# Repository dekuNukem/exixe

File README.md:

# exixe: Low-cost miniature Nixie tube driver modules

[Get exixe](https://www.tindie.com/products/dekuNukem/exixe-miniture-nixie-tube-driver-modules/) | [User manual](getting_started.md)

exixe is a miniature driver module for IN-12 and IN-14 Nixie tubes.

It aims to simplify Nixie tube related projects by eliminating the need for obscure vintage driver chips and multiplexing circuits. Instead, you can control every digit and the RGB backlight via SPI using only 3 wires and 1 line of code.

exixe is cheap, small and modular for easy integration. It is compatible with Arduino, Raspberry Pi, and virtually all embedded dev boards today.

## Buy exixe on Tindie!

I did a small production run of exixe modules, and now you can buy them directly on Tindie:

https://www.tindie.com/products/dekuNukem/exixe-miniture-nixie-tube-driver-modules/

## Features

Compared to the traditional approach, exixe modules offers significant advantages:

#### Small and modular
* 2x4 cm (0.79x1.57 inches)
* Breadboard friendly
* Easy integration
* Reusable

#### SPI interface
* High speed, up to 24MHz SCLK
* Simple 16-byte command packet
* Available on virtually all embedded systems including Arduino and Raspberry Pi

#### Advanced control
* RGB backlight
* 128 brightness levels
* Hardware PWM on all cathodes and LEDs for smooth dimming and animations

#### Tube overdrive
* Optionally allows twice the cathode current
* For poisoned cathodes in second-hand tubes
* [Before](resources/no_overdrive.jpg) and [after](resources/with_overdrive.jpg).

#### No multiplexing
* Brighter display
* Longer tube life
* Simpler design
* Lower power consumption

## Getting started

Please see [getting_started.md](/getting_started.md)

## Arduino Library

Please [click here](arduino_library)

## Raspberry Pi/Python Library

Please [click here](python_library)

## Pinout, SPI command format and technical details

Please see [technical_details.md](/technical_details.md)

## Supported tubes

exixe-14 module is primarily designed for IN-14 Nixie tubes, but will also work with IN-16 and IN-19 tubes.

exixe-12 module is primarily designed for IN-12 Nixie tubes, but works with IN-15 tubes as well.

## Using other tubes

You can also use exixe module with unsupported tubes, with some modification.

Please see [unsupported_tubes.md](/unsupported_tubes.md)

## Making some yourself

Please see [making_some.md](/making_some.md)

## Contact

Questions? Feel free to [open an issue](https://github.com/dekuNukem/exixe/issues). This is the preferred way since it helps other people too.

You can also email me at `dekunukem gmail com` for inquires.

## More photos

exixe-12 working with an Arduino Micro, showing a smooth crossfade animation:

exixe-14 in action on a [finished clock](https://github.com/dekuNukem/exixe_clock):

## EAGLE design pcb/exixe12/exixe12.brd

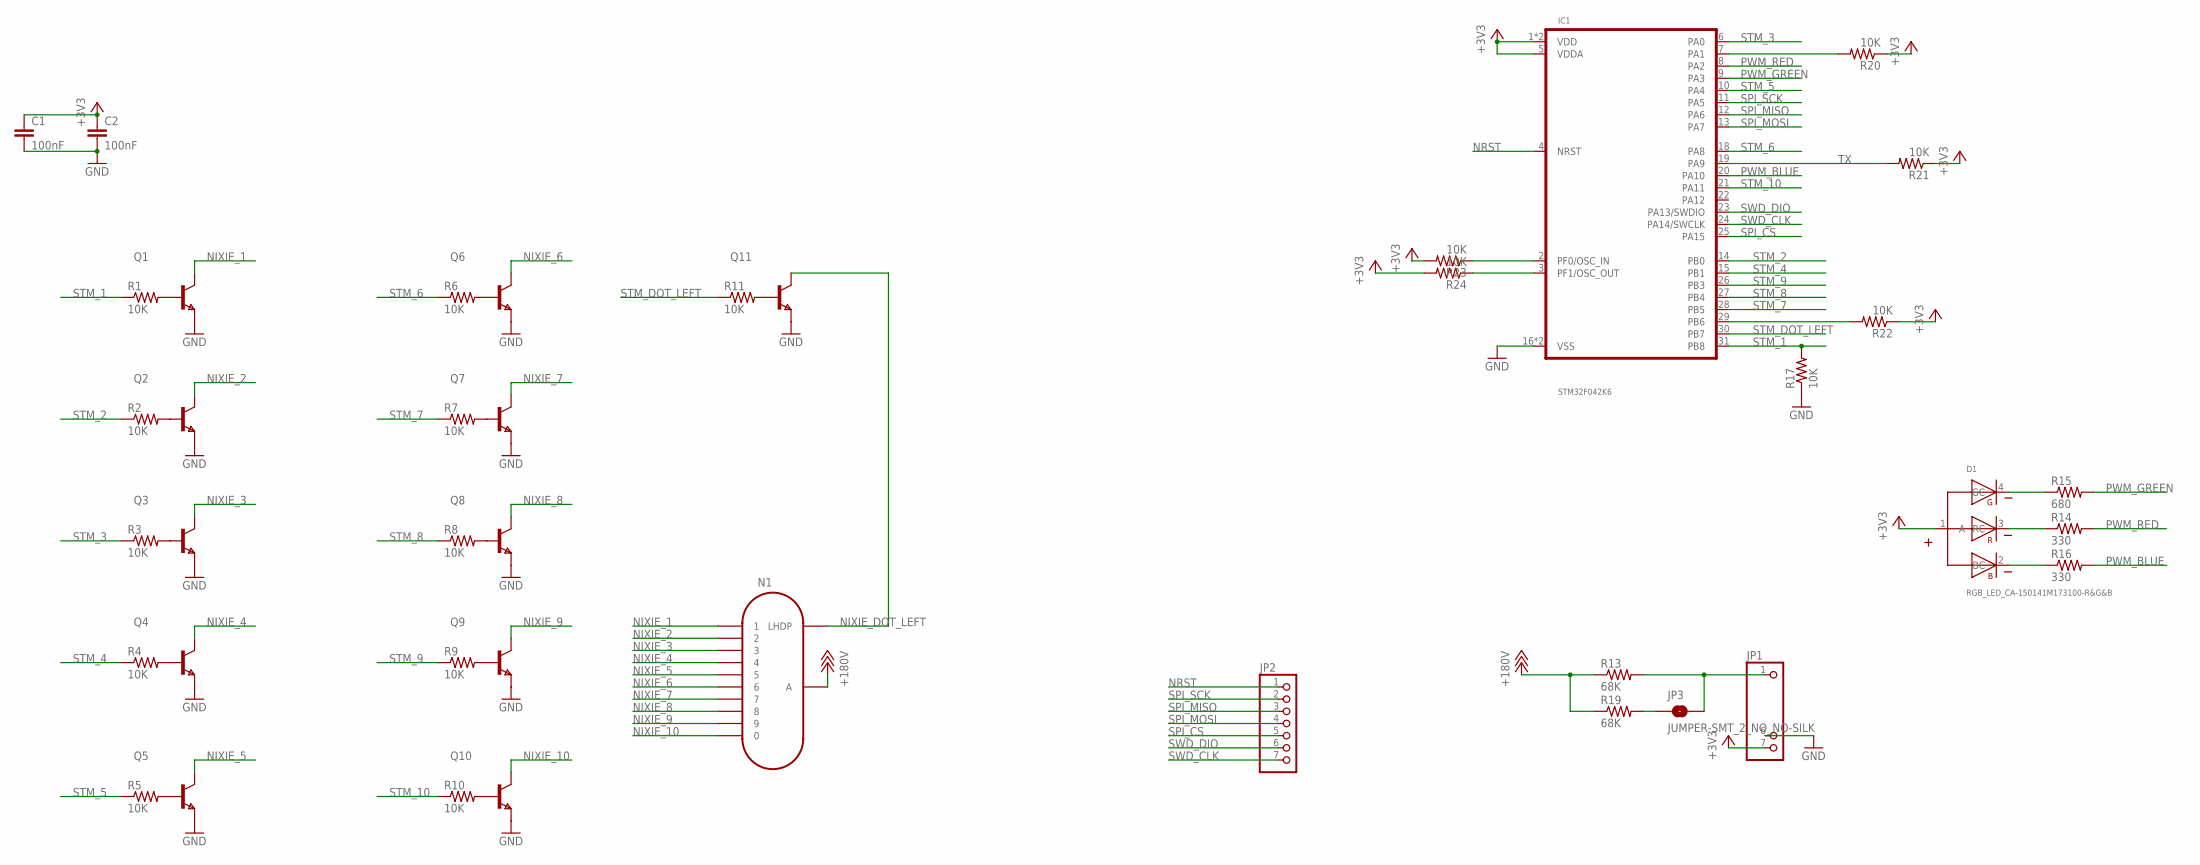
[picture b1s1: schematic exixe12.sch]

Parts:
C1, C2: 100nF; 0805
D1: RGB_LED_CA-150141M173100-R&G&B; 3528-COMMON-ANODE
IC1: STM32F042K6; TQFP32-08
JP1, JP2: PINHD-1X7; 1X07
JP3: JUMPER-SMT_2_NO_NO-SILK; SMT-JUMPER_2_NO_NO-SILK
N1: IN-12B; IN-12
Q1, Q2, Q3, Q4, Q5, Q6, Q7, Q8, Q9, Q10, Q11: BF820; SOT323
R1, R2, R3, R4, R5, R6, R7, R8, R9, R10, R11, R17, R20, R21, R22, R23, R24: 10K; 0805
R13, R19: 68K; 0805
R14, R16: 330; 0805
R15: 680; 0805

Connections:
+3V3: C1.1, C2.1, D1.1 (A), IC1.1 (VDD), IC1.5 (VDDA), IC1.17 (VDD), JP1.7, R20.1, R21.1, R22.1, R23.2, R24.2
+180V: N1.A, R13.1, R19.1
GND: C1.2, C2.2, IC1.16 (VSS), IC1.32 (VSS), JP1.6, Q1.2 (E), Q2.2 (E), Q3.2 (E), Q4.2 (E), Q5.2 (E), Q6.2 (E), Q7.2 (E), Q8.2 (E), Q9.2 (E), Q10.2 (E), Q11.2 (E), R17.1
unnamed: Q1.1 (B), R1.2
unnamed: JP3.1, R19.2
unnamed: D1.4 (GC), R15.1
unnamed: Q2.1 (B), R2.2
unnamed: Q3.1 (B), R3.2
unnamed: Q4.1 (B), R4.2
unnamed: Q5.1 (B), R5.2
unnamed: Q6.1 (B), R6.2
unnamed: Q7.1 (B), R7.2
unnamed: Q8.1 (B), R8.2
unnamed: Q9.1 (B), R9.2
unnamed: Q10.1 (B), R10.2
unnamed: Q11.1 (B), R11.2
unnamed: IC1.29 (PB6), R22.2
unnamed: D1.3 (RC), R14.1
unnamed: IC1.2 (PF0/OSC_IN), R23.1
unnamed: IC1.3 (PF1/OSC_OUT), R24.1
unnamed: JP1.1, JP3.2, R13.2
unnamed: IC1.7 (PA1), R20.2
unnamed: D1.2 (BC), R16.1
NIXIE_1: N1.1, Q1.3 (C)
NIXIE_2: N1.2, Q2.3 (C)
NIXIE_3: N1.3, Q3.3 (C)
NIXIE_4: N1.4, Q4.3 (C)
NIXIE_5: N1.5, Q5.3 (C)
NIXIE_6: N1.6, Q6.3 (C)
NIXIE_7: N1.7, Q7.3 (C)
NIXIE_8: N1.8, Q8.3 (C)
NIXIE_9: N1.9, Q9.3 (C)
NIXIE_10: N1.0, Q10.3 (C)
NIXIE_DOT_LEFT: N1.LHDP, Q11.3 (C)
NRST: IC1.4 (NRST), JP2.1
PWM_BLUE: IC1.20 (PA10), R16.2
PWM_GREEN: IC1.9 (PA3), R15.2
PWM_RED: IC1.8 (PA2), R14.2
SPI_CS: IC1.25 (PA15), JP2.5
SPI_MISO: IC1.12 (PA6), JP2.3
SPI_MOSI: IC1.13 (PA7), JP2.4
SPI_SCK: IC1.11 (PA5), JP2.2
STM_1: IC1.31 (PB8), R1.1, R17.2
STM_2: IC1.14 (PB0), R2.1
STM_3: IC1.6 (PA0), R3.1
STM_4: IC1.15 (PB1), R4.1
STM_5: IC1.10 (PA4), R5.1
STM_6: IC1.18 (PA8), R6.1
STM_7: IC1.28 (PB5), R7.1
STM_8: IC1.27 (PB4), R8.1
STM_9: IC1.26 (PB3), R9.1
STM_10: IC1.21 (PA11), R10.1
STM_DOT_LEFT: IC1.30 (PB7), R11.1
SWD_CLK: IC1.24 (PA14/SWCLK), JP2.7
SWD_DIO: IC1.23 (PA13/SWDIO), JP2.6
TX: IC1.19 (PA9), R21.2

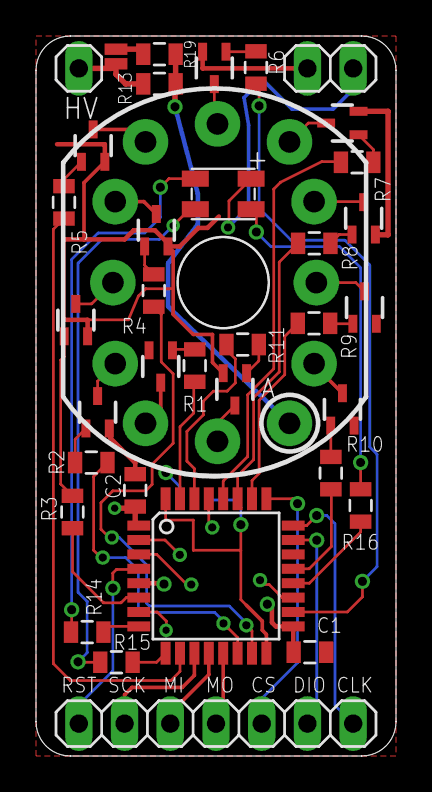
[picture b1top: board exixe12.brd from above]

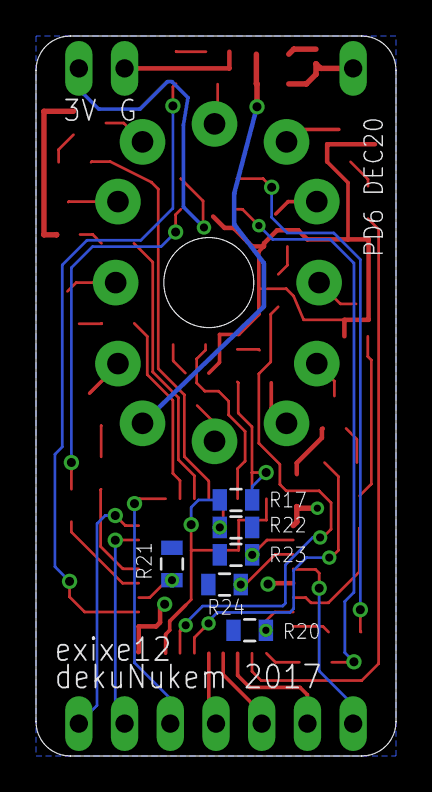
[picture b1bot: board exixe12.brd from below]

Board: 2 copper layers, 20.0 x 40.0 mm, 41 parts (6 on the bottom side), 56 nets.

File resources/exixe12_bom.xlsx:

Part | Value | Device | Package | Description
C1 | 1uF | CAP0805 | 0805 | Capacitor
C2 | 100nF | CAP0805 | 0805 | Capacitor
D1 | RGB LED | RGB_LED | 3528-COMMON-ANODE | SMD full-color LED
JP1 |  | PINHD-1X7 | 1X07 | PIN HEADER
JP2 |  | PINHD-1X7 | 1X07 | PIN HEADER
N1 | IN-12B | IN-12B | IN-12 | IN-12B: medium numeric topview nixie tube
Q1 |  | BF820 | SOT323 | NPN TRANSISTOR
Q2 |  | BF820 | SOT323 | NPN TRANSISTOR
Q3 |  | BF820 | SOT323 | NPN TRANSISTOR
Q4 |  | BF820 | SOT323 | NPN TRANSISTOR
Q5 |  | BF820 | SOT323 | NPN TRANSISTOR
Q6 |  | BF820 | SOT323 | NPN TRANSISTOR
Q7 |  | BF820 | SOT323 | NPN TRANSISTOR
Q8 |  | BF820 | SOT323 | NPN TRANSISTOR
Q9 |  | BF820 | SOT323 | NPN TRANSISTOR
Q10 |  | BF820 | SOT323 | NPN TRANSISTOR
Q11 |  | BF820 | SOT323 | NPN TRANSISTOR
R1 | 10K | RESISTOR0805-RES | 0805 | Resistor
R2 | 10K | RESISTOR0805-RES | 0805 | Resistor
R3 | 10K | RESISTOR0805-RES | 0805 | Resistor
R4 | 10K | RESISTOR0805-RES | 0805 | Resistor
R5 | 10K | RESISTOR0805-RES | 0805 | Resistor
R6 | 10K | RESISTOR0805-RES | 0805 | Resistor
R7 | 10K | RESISTOR0805-RES | 0805 | Resistor
R8 | 10K | RESISTOR0805-RES | 0805 | Resistor
R9 | 10K | RESISTOR0805-RES | 0805 | Resistor
R10 | 10K | RESISTOR0805-RES | 0805 | Resistor
R11 | 10K | RESISTOR0805-RES | 0805 | Resistor
R12 | 68K | RESISTOR0805-RES | 0805 | Resistor
R13 | 68K | RESISTOR0805-RES | 0805 | Resistor
R14 | 330 | RESISTOR0805-RES | 0805 | Resistor
R15 | 680 | RESISTOR0805-RES | 0805 | Resistor
R16 | 330 | RESISTOR0805-RES | 0805 | Resistor
R17 | 68K | RESISTOR0805-RES | 0805 | Resistor
R18 | 10K | RESISTOR0805-RES | 0805 | Resistor
R19 | 68K | RESISTOR0805-RES | 0805 | Resistor
U$2 | STM32F042K6T6 | STM32F042K6T6 | TQFP32-08 | STM32 microcontroller

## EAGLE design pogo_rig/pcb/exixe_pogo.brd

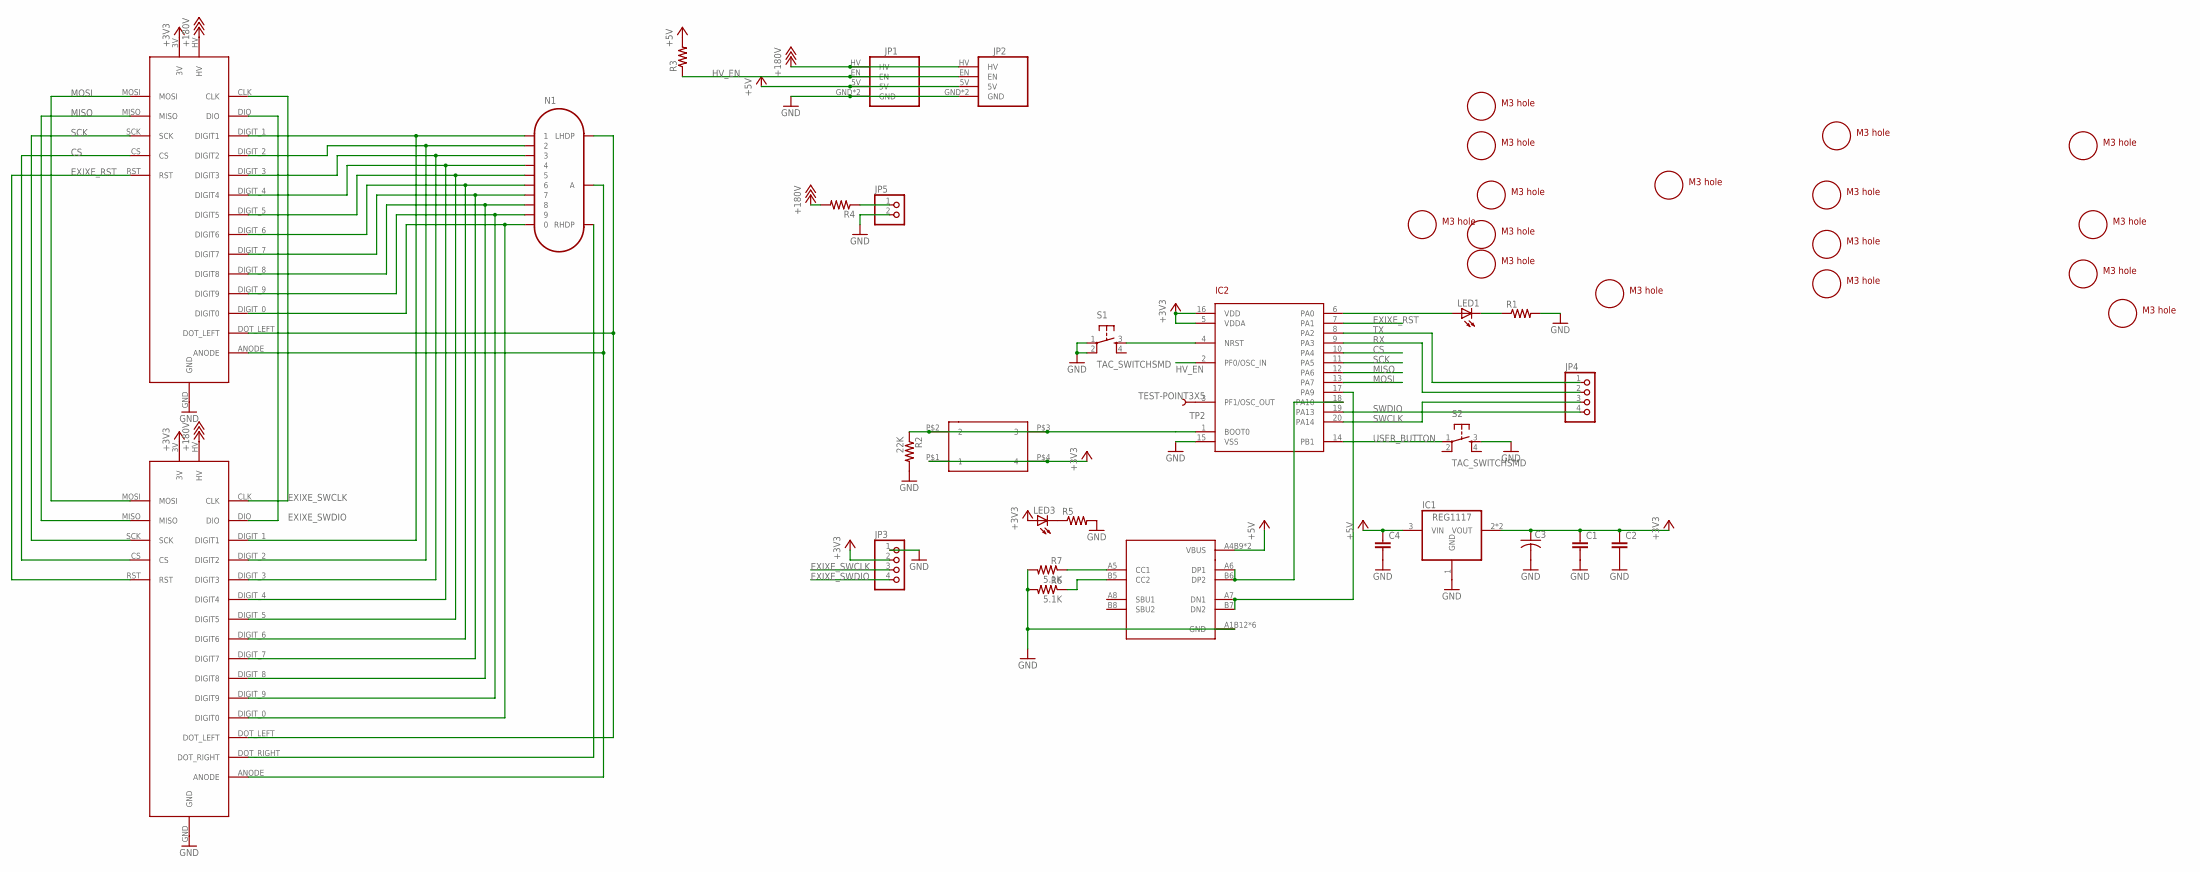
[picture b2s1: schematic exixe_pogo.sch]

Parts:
C1, C2, C4: CAP0805; 0805
C3: C-USC1210; C1210
IC1: REG1117; SOT223
IC2: STM32F030F4; TSSOP20
JP1: EBAY_MODULEEBAY; EBAY_PKG
JP2: EBAY_MODULETAOBAO; TAOBAO_PKG
JP3, JP4: PINHD-1X4; 1X04
JP5: PINHD-1X2; 1X02
LED1, LED3: LEDCHIP-LED0805; CHIP-LED0805
N1: IN-14
R1, R3, R4, R5: RESISTOR0805-RES; 0805
R2: 22K; 0805
R6, R7: 5.1K; 0805
S1, S2: TAC_SWITCHSMD; TACTILE-SWITCH-SMD
SW2: 324_SW324_SWITCH_FOOT_HOLE; 342_SWICH_FOOT_HOLE
TP2: TEST-POINT3X5; PAD.03X.05
U1: USBC_16P_CENTERED; USBC_16P_FOOT
U$1: EXIXE12_POGO; EXIXE12_PAC
U$2: EXIXE14_POGO; EXIXE14_PAC
U$3, U$4, U$5, U$6, U$7, U$8, U$9, U$10, U$11, U$12, U$13, U$14, U$15, U$16, U$17, U$18: M3_MOUNTING_HOLE; M3_MOUNTING_HOLE_PACK

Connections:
+3V3: C1.1, C2.1, C3.1, IC1.2 (VOUT), IC1.4 (VOUT), IC2.5 (VDDA), IC2.16 (VDD), JP3.2, LED3.A, SW2.P$1 (1), SW2.P$4 (4), U$1.3V, U$2.3V
+5V: C4.1, IC1.3 (VIN), JP1.5V, JP2.5V, R3.2, U1.A4B9 (VBUS), U1.B4A9 (VBUS)
+180V: JP1.HV, JP2.HV, R4.2, U$1.HV, U$2.HV
CS: IC2.10 (PA4), U$1.CS, U$2.CS
EXIXE_RST: IC2.7 (PA1), U$1.RST, U$2.RST
EXIXE_SWCLK: JP3.3, U$1.CLK, U$2.CLK
EXIXE_SWDIO: JP3.4, U$1.DIO, U$2.DIO
GND: C1.2, C2.2, C3.2, C4.2, IC1.1 (GND), IC2.15 (VSS), JP1.GND, JP1.GND2 (GND), JP2.GND, JP2.GND2 (GND), JP3.1, JP5.2, R1.2, R2.2, R5.2, R6.2, R7.2, S1.1, S1.2, S2.3, U1.A1B12 (GND), U1.B11A12 (GND), U1.P$13 (GND), U1.P$14 (GND), U1.P$15 (GND), U1.P$16 (GND), U$1.GND, U$2.GND
HV_EN: IC2.2 (PF0/OSC_IN), JP1.EN, JP2.EN, R3.1
MISO: IC2.12 (PA6), U$1.MISO, U$2.MISO
MOSI: IC2.13 (PA7), U$1.MOSI, U$2.MOSI
unnamed: N1.1, U$1.DIGIT_1 (DIGIT1), U$2.DIGIT_1 (DIGIT1)
unnamed: IC2.4 (NRST), S1.3
unnamed: N1.2, U$1.DIGIT_2 (DIGIT2), U$2.DIGIT_2 (DIGIT2)
unnamed: N1.3, U$1.DIGIT_3 (DIGIT3), U$2.DIGIT_3 (DIGIT3)
unnamed: N1.4, U$1.DIGIT_4 (DIGIT4), U$2.DIGIT_4 (DIGIT4)
unnamed: N1.5, U$1.DIGIT_5 (DIGIT5), U$2.DIGIT_5 (DIGIT5)
unnamed: N1.6, U$1.DIGIT_6 (DIGIT6), U$2.DIGIT_6 (DIGIT6)
unnamed: N1.7, U$1.DIGIT_7 (DIGIT7), U$2.DIGIT_7 (DIGIT7)
unnamed: N1.8, U$1.DIGIT_8 (DIGIT8), U$2.DIGIT_8 (DIGIT8)
unnamed: N1.9, U$1.DIGIT_9 (DIGIT9), U$2.DIGIT_9 (DIGIT9)
unnamed: N1.0, U$1.DIGIT_0 (DIGIT0), U$2.DIGIT_0 (DIGIT0)
unnamed: N1.RHDP, U$2.DOT_RIGHT
unnamed: N1.LHDP, U$1.DOT_LEFT, U$2.DOT_LEFT
unnamed: N1.A, U$1.ANODE, U$2.ANODE
unnamed: LED1.C, R1.1
unnamed: IC2.6 (PA0), LED1.A
unnamed: JP5.1, R4.1
unnamed: IC2.18 (PA10), U1.A6 (DP1), U1.B6 (DP2)
unnamed: IC2.17 (PA9), U1.A7 (DN1), U1.B7 (DN2)
unnamed: IC2.3 (PF1/OSC_OUT), TP2.P$1
unnamed: IC2.1 (BOOT0), R2.1, SW2.P$2 (2), SW2.P$3 (3)
unnamed: R6.1, U1.B5 (CC2)
unnamed: R7.1, U1.A5 (CC1)
unnamed: LED3.C, R5.1
RX: IC2.9 (PA3), JP4.2
SCK: IC2.11 (PA5), U$1.SCK, U$2.SCK
SWCLK: IC2.20 (PA14), JP4.3
SWDIO: IC2.19 (PA13), JP4.4
TX: IC2.8 (PA2), JP4.1
USER_BUTTON: IC2.14 (PB1), S2.1

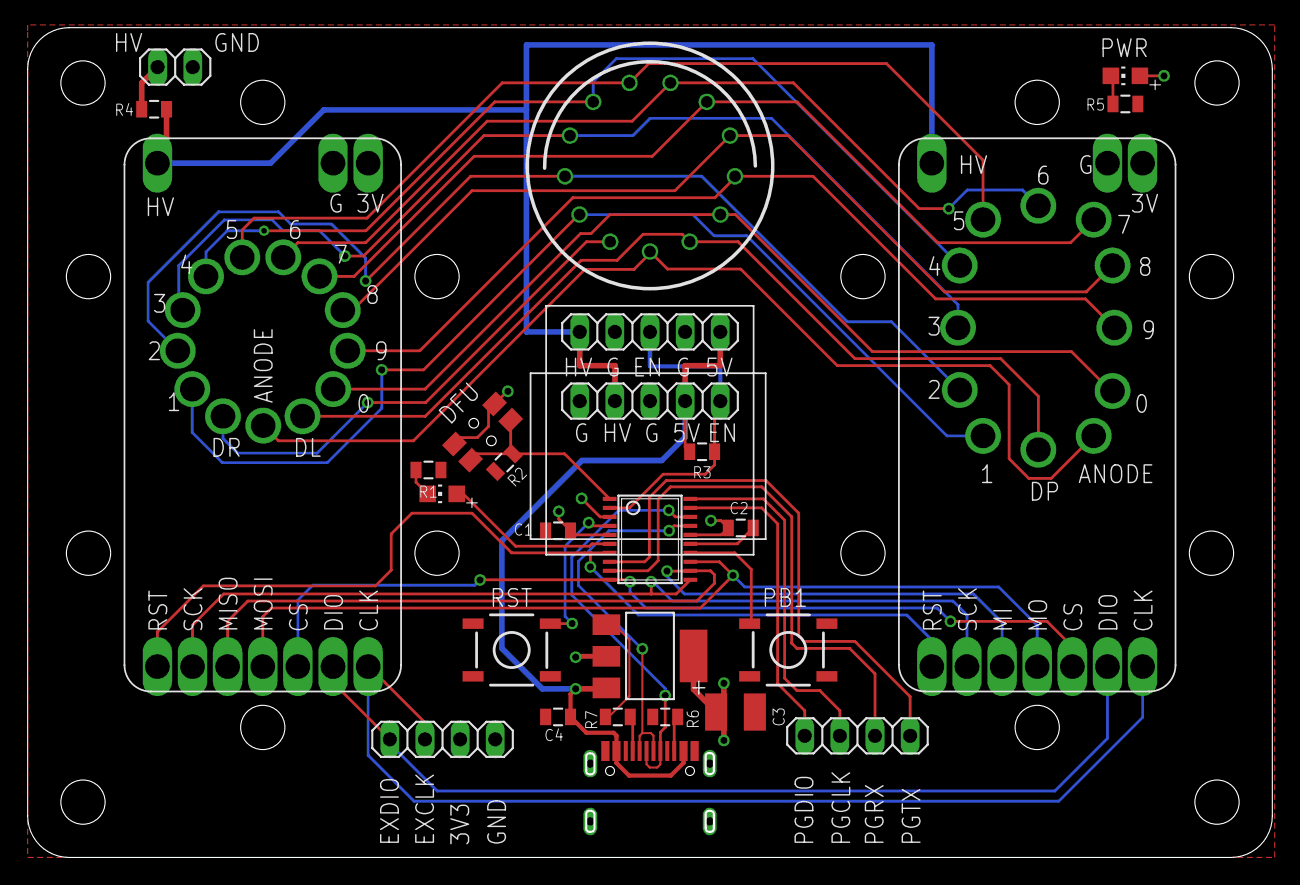
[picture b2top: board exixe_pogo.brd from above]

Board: 2 copper layers, 90.0 x 60.0 mm, 44 parts (1 on the bottom side), 41 nets.

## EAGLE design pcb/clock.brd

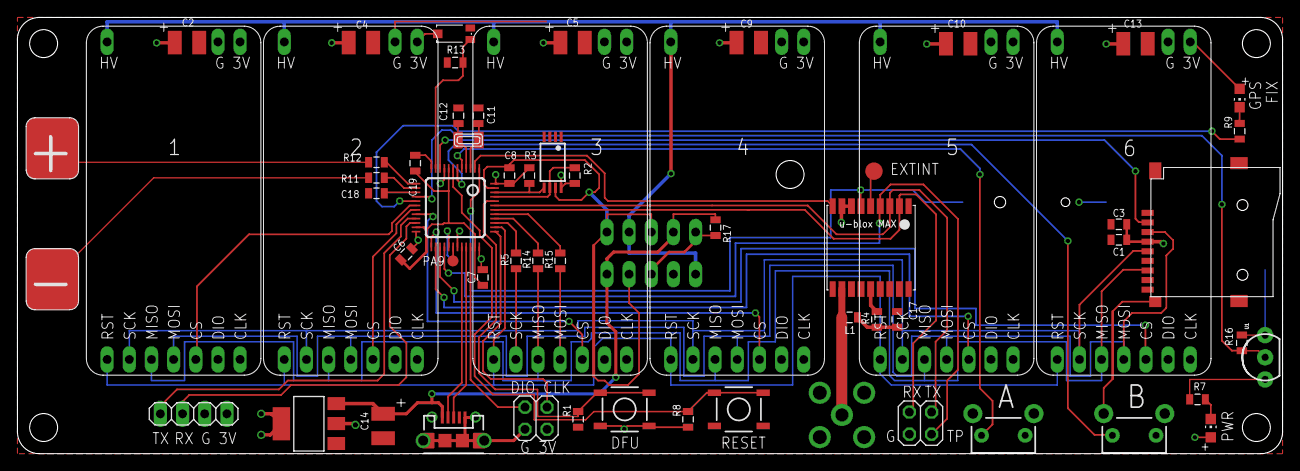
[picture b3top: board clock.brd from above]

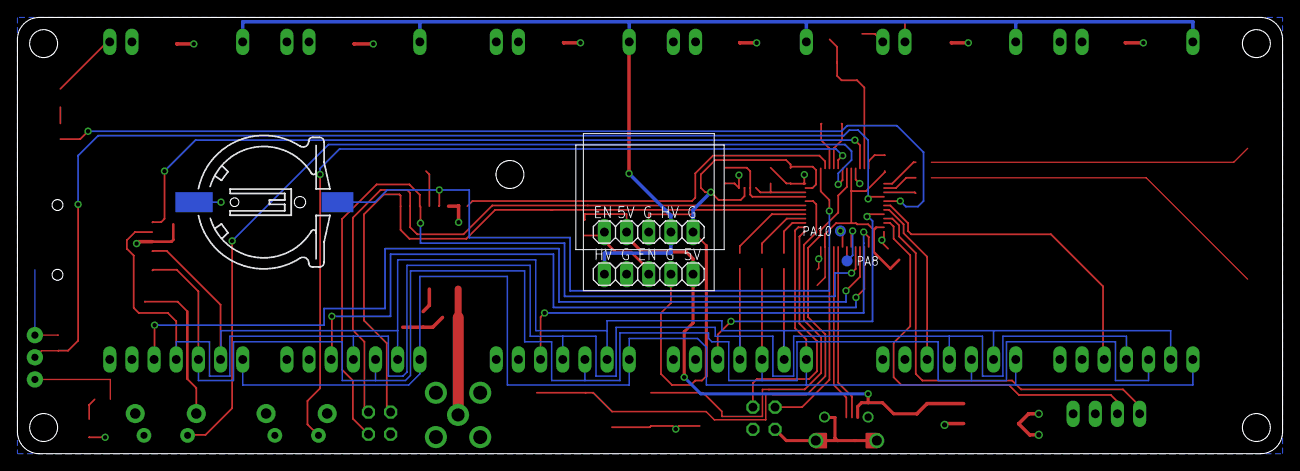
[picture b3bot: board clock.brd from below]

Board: 2 copper layers, 145.0 x 50.0 mm, 72 parts (5 on the bottom side), 56 nets.

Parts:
C1, C3, C6, C7, C8, C11, C12, C17, C18, C19: 0805
C2, C4, C5, C9, C10, C13, C14: C1210
G1: CH291-1220LF
IC1: STM32F072C8T6; TQFP48
IC2: REG1117; SOT223
IC3: 24C64ST; TSSOP8
JP1: EBAY_PKG
JP2: TAOBAO_PKG
JP3, JP4: 2X02
JP5: 1X04
L1: 0805
LED2: CHIP-LED0805
PWR: CHIP-LED0805
R1, R2, R3, R4, R5, R7, R8, R9, R11, R12, R13, R14, R15, R16, R17: 0805
S1, S2: TAC_SWITCHSMD; TACTILE-SWITCH-SMD
S4, S5: SWITCH-MOMENTARY-2SIDE_EZ; TACTILE-PTH-SIDEEZ
SD1: TF-HOLDER; TF-PULL
TP1: PTR1TP20R; TP20R
TP2, TP3, TP4: TEST-POINT3X5; PAD.03X.05
U1: DS18B20; TO-92-AMMO
U$1, U$2, U$3, U$4, U$5, U$6: EXIXE; EXIXE_PAC
U$7: MAX-M8
U$8: TEMT6000; TEMT6000-SEN
U$10, U$11, U$12, U$13, U$20: M3_MOUNTING_HOLE; M3_MOUNTING_HOLE_PACK
U$14, U$15: TOUCHPAD; TOUCHPAD_PAK
X1: SMA90_DIP
X2: XTAL3215
X3: USB-MICROB

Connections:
+3V3: C1.1, C2.1, C3.1, C4.1, C5.1, C6.1, C7.1, C8.1, C9.1, C10.1, C13.1, IC1.9, IC1.24, IC1.36, IC1.48, IC2.2, IC2.4, IC3.8, JP3.3, JP5.4, LED2.A, PWR.A, R2.2, R3.2, R8.2, R16.2, S1.3, S1.4, SD1.4, U1.3, U$1.3V, U$2.3V, U$3.3V, U$4.3V, U$5.3V, U$6.3V, U$7.7_VCC_IO, U$7.8_VCC, U$8.COLLECTOR
+5V: C14.1, IC2.3, JP1.5V, JP2.5V, R17.2, X3.VBUS
+180V: JP1.HV, JP2.HV, U$1.HV, U$2.HV, U$3.HV, U$4.HV, U$5.HV, U$6.HV
A_BUTTON: IC1.5, S4.1
B_BUTTON: IC1.6, S5.1
DS18B20_DATA: IC1.16, R16.1, U1.2
EXIXE1_CS: IC1.18, U$1.CS
EXIXE2_CS: IC1.19, U$2.CS
EXIXE3_CS: IC1.20, U$3.CS
EXIXE4_CS: IC1.25, U$4.CS
EXIXE5_CS: IC1.26, U$5.CS
EXIXE6_CS: IC1.27, U$6.CS
EXIXE_RESET: IC1.38, U$1.RST, U$2.RST, U$3.RST, U$4.RST, U$5.RST, U$6.RST
GND: C1.2, C2.2, C3.2, C4.2, C5.2, C6.2, C7.2, C8.2, C9.2, C10.2, C11.2, C12.2, C13.2, C14.2, C17.2, C18.1, C19.2, G1.-, IC1.8, IC1.23, IC1.35, IC1.47, IC2.1, IC3.1, IC3.2, IC3.3, IC3.4, IC3.7, JP1.GND, JP1.GND2, JP2.GND, JP2.GND2, JP3.1, JP4.1, JP5.3, R1.2, R7.1, R13.1, S2.3, S2.4, S4.2, S4.ANCHOR1, S4.ANCHOR2, S5.2, S5.ANCHOR1, S5.ANCHOR2, SD1.6, SD1.S1, SD1.S2, SD1.S3, SD1.S4, U1.1, U$1.GND, U$2.GND, U$3.GND, U$4.GND, U$5.GND, U$6.GND, U$7.1_GND, U$7.10_GND, U$7.12_GND, X1.GND1, X1.GND2, X1.GND3, X1.GND4, X3.GND, X3.P1, X3.P2, X3.P3, X3.P4, X3.P5, X3.P6
GPS_FIX_LED: IC1.17, R9.2
GPS_RESET: IC1.2, U$7.9_RESET_N
GPS_TP: IC1.28, JP4.3, U$7.4_TIMEPULSE
I2C_SCL: IC1.45, IC3.6, R2.1
I2C_SDA: IC1.46, IC3.5, R3.1
LIGHT_SENSOR_OUTPUT: IC1.11, R13.2, U$8.EMITTER
unnamed: C11.1, IC1.3, X2.P$2
unnamed: C12.1, IC1.4, X2.P$1
unnamed: IC1.7, R8.1, S2.1, S2.2
unnamed: L1.1, U$7.11_RF_IN, X1.ANTENNA
unnamed: IC1.44, R1.1, S1.1, S1.2
unnamed: IC1.31, TP2.P$1
unnamed: IC1.30, TP3.P$1
unnamed: IC1.14, R11.1
unnamed: R11.2, U$15.P$1
unnamed: R12.2, U$14.P$1
unnamed: IC1.13, R12.1
unnamed: C17.1, L1.2, R4.2
unnamed: R4.1, U$7.14_VCC_RF
unnamed: C18.2, IC1.15
unnamed: IC1.29, TP4.P$1
unnamed: IC1.39, R5.1
unnamed: C19.1, IC1.12
unnamed: IC1.41, R15.1
unnamed: IC1.40, R14.1
unnamed: LED2.C, R9.1
unnamed: TP1.TP, U$7.5_EXTINT
unnamed: PWR.C, R7.2
NIXIE_PWR_EN: JP1.EN, JP2.EN, R17.1
PB10: IC1.21, JP5.1
PB11: IC1.22, JP5.2
SD_CS: IC1.10, SD1.2
SPI1_MISO: R14.2, SD1.7, U$1.MISO, U$2.MISO, U$3.MISO, U$4.MISO, U$5.MISO, U$6.MISO
SPI1_MOSI: R15.2, SD1.3, U$1.MOSI, U$2.MOSI, U$3.MOSI, U$4.MOSI, U$5.MOSI, U$6.MOSI
SPI1_SCK: R5.2, SD1.5, U$1.SCK, U$2.SCK, U$3.SCK, U$4.SCK, U$5.SCK, U$6.SCK
SWCLK: IC1.37, JP3.4
SWDIO: IC1.34, JP3.2
USART1_RX: IC1.43, JP4.4, U$7.3_RXD
USART1_TX: IC1.42, JP4.2, U$7.2_TXD
USB_DM: IC1.32, X3.D-
USB_DP: IC1.33, X3.D+
VBAT: G1.+, IC1.1, U$7.6_V_BCKP

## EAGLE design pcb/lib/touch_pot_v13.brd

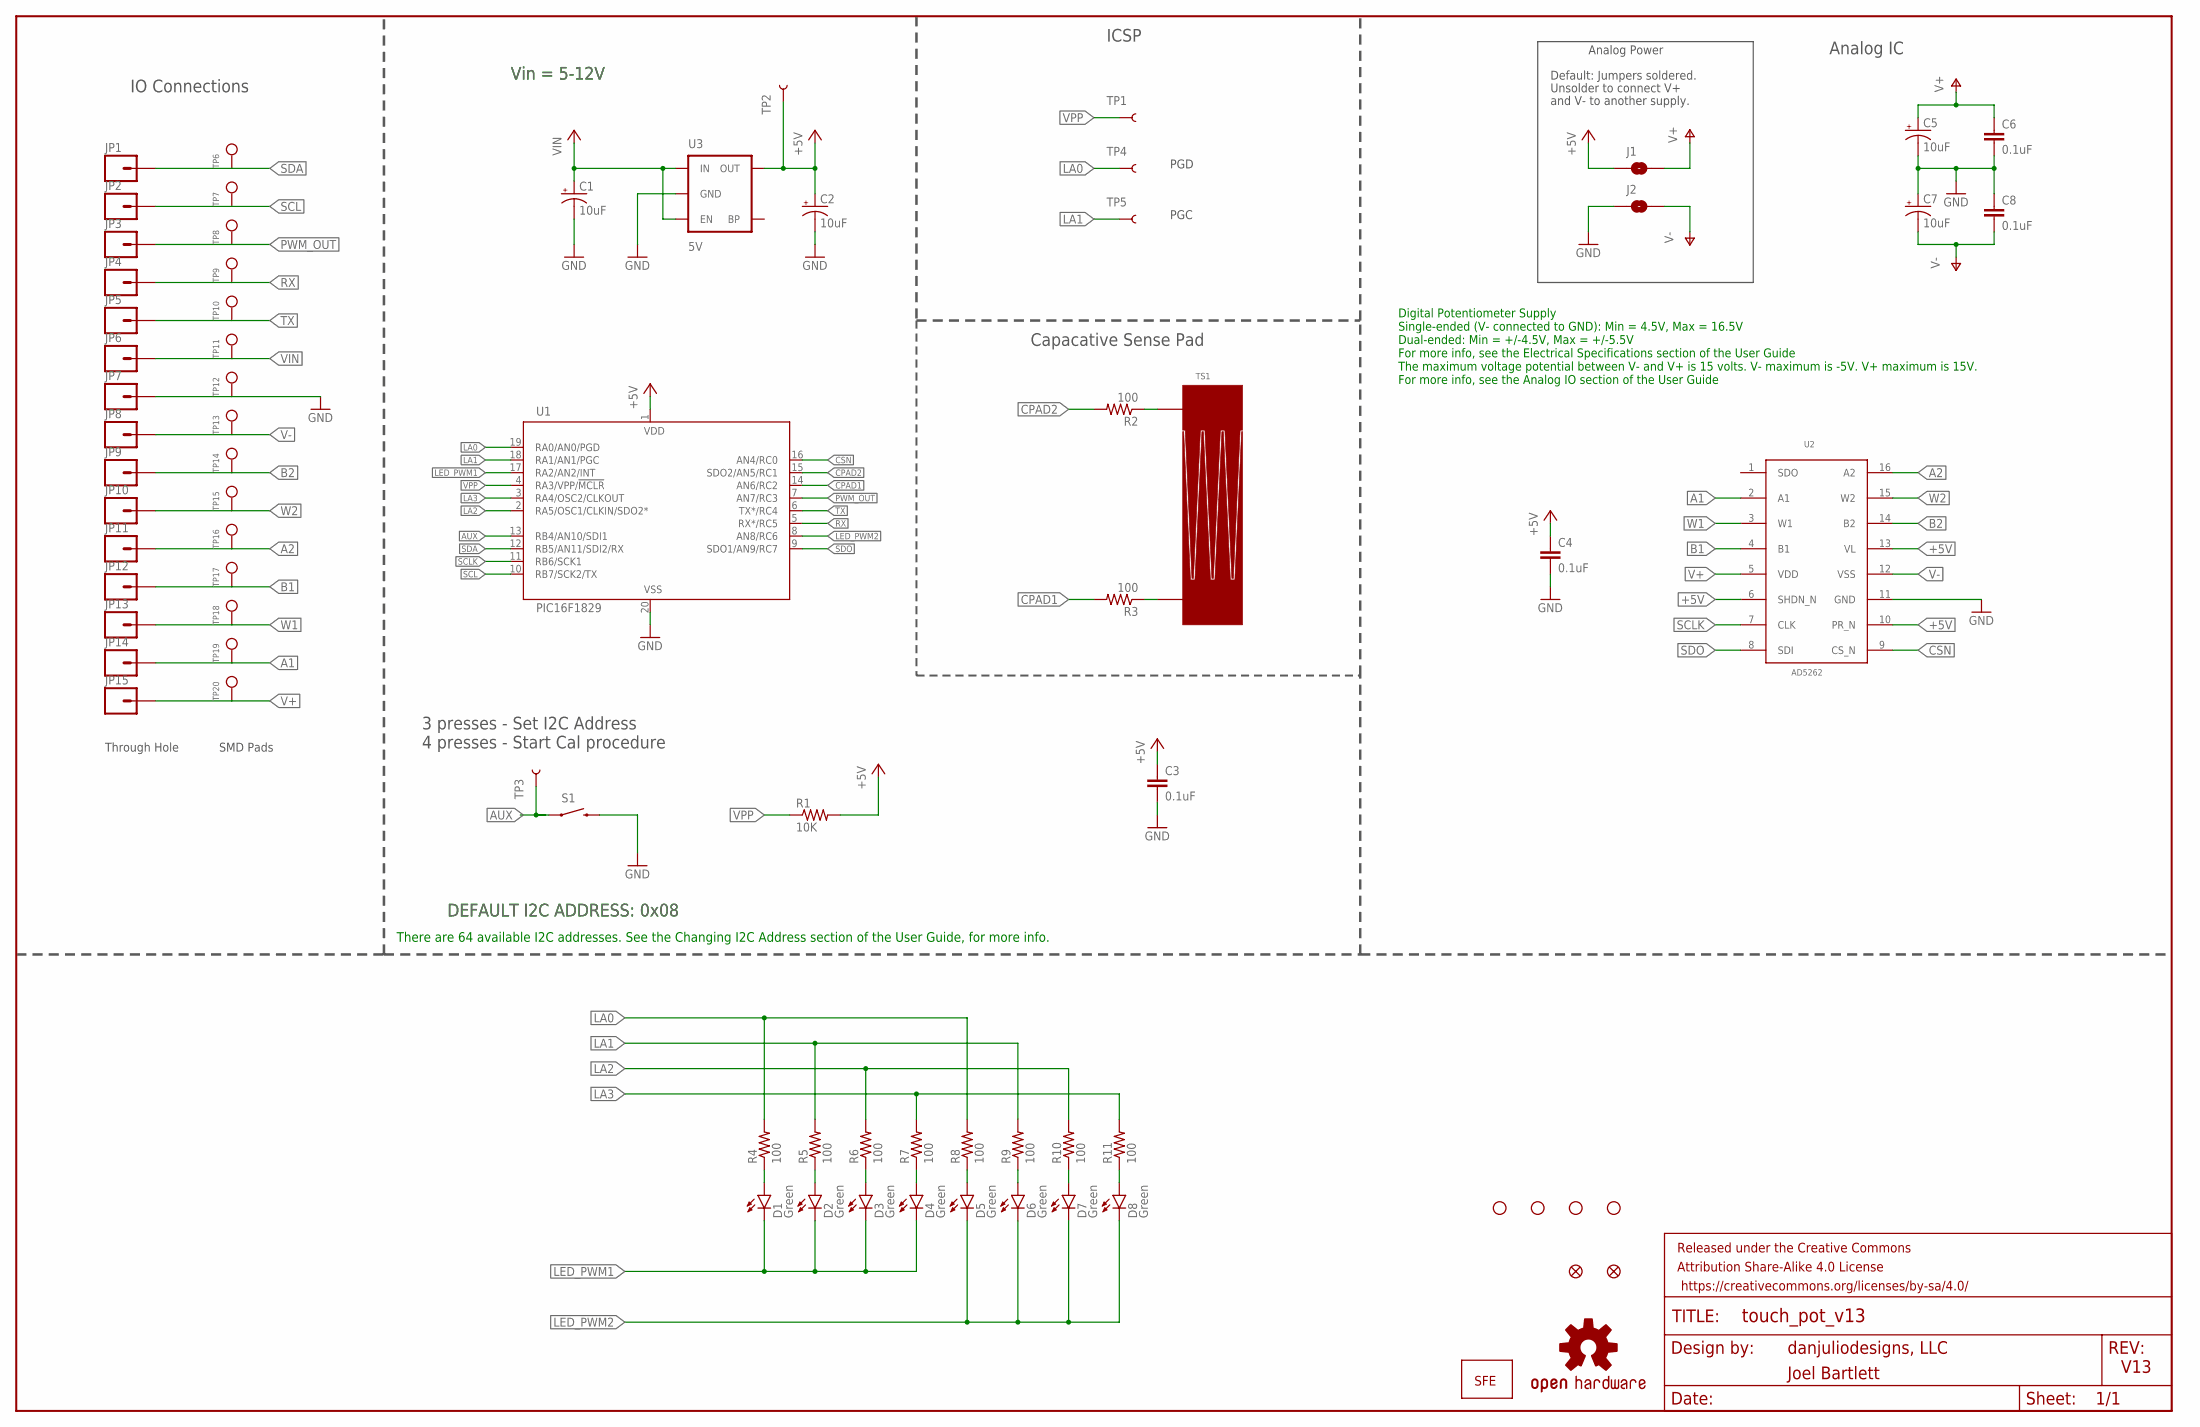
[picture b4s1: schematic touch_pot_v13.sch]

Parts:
C1, C2, C5, C7: 10uF; EIA3216
C3, C4, C6, C8: 0.1uF; 0603-CAP
D1, D2, D3, D4, D5, D6, D7, D8: Green; LED-1206-BOTTOM
FID1, FID2: FIDUCIAL1X2; FIDUCIAL-1X2
FRAME3: FRAME-LEDGER; CREATIVE_COMMONS
J1, J2: SJCLOSED; SJ_2S
JP1, JP2, JP3, JP4, JP5, JP6, JP7, JP8, JP9, JP10, JP11, JP12, JP13, JP14, JP15: M01SMDNS; 1X01NS
R1: 10K; 0603-RES
R2, R3, R4, R5, R6, R7, R8, R9, R10, R11: 100; 0603-RES
S1: SWITCH-MOMENTARY-2SMD; TACTILE-SWITCH-SMD
STANDOFF1, STANDOFF2, STANDOFF3, STANDOFF4: STAND-OFFTIGHT; STAND-OFF-TIGHT
TP1, TP2, TP3, TP4, TP5: TEST-POINT3X4; PAD.03X.04
TP6, TP7, TP8, TP9, TP10, TP11, TP12, TP13, TP14, TP15, TP16, TP17, TP18, TP19, TP20: SINGLE_PADSMD; 2MM_SMD_PAD
TS1: 2CH_LINEAR_TOUCH; 2CH_48MM_LINEAR_TOUCH
U1: PIC16F1829; SSOP20
U2: AD5262; SSOP16
U3: 5V; SOT23-5
U$4: OSHW-LOGOM; OSHW-LOGO-M
U$5: SFE_LOGO_NAME_WEB; SFE-NEW-WEBLOGO

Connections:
+5V: C2.A (+), C3.1, C4.1, J1.1, R1.2, TP2.P$1, U1.1 (VDD), U2.6 (SHDN_N), U2.10 (PR_N), U2.13 (VL), U3.5 (OUT)
A1: JP14.1, TP19.P$1, U2.2 (A1)
A2: JP11.1, TP16.P$1, U2.16 (A2)
AUX: S1.1, TP3.P$1, U1.13 (RB4/AN10/SDI1)
B1: JP12.1, TP17.P$1, U2.4 (B1)
B2: JP9.1, TP14.P$1, U2.14 (B2)
CPAD1: R3.2, U1.14 (AN6/RC2)
CPAD2: R2.2, U1.15 (SDO2/AN5/RC1)
CSN: U1.16 (AN4/RC0), U2.9 (CS_N)
GND: C1.C (-), C2.C (-), C3.2, C4.2, C5.C (-), C6.2, C7.A (+), C8.1, J2.1, JP7.1, S1.3 (2), TP12.P$1, U1.20 (VSS), U2.11 (GND), U3.2 (GND)
LA0: R4.2, R8.2, TP4.P$1, U1.19 (RA0/AN0/PGD)
LA1: R5.2, R9.2, TP5.P$1, U1.18 (RA1/AN1/PGC)
LA2: R6.2, R10.2, U1.2 (RA5/OSC1/CLKIN/SDO2*)
LA3: R7.2, R11.2, U1.3 (RA4/OSC2/CLKOUT)
LED_PWM1: D1.C, D2.C, D3.C, D4.C, U1.17 (RA2/AN2/INT)
LED_PWM2: D5.C, D6.C, D7.C, D8.C, U1.8 (AN8/RC6)
unnamed: D1.A, R4.1
unnamed: D2.A, R5.1
unnamed: D3.A, R6.1
unnamed: D4.A, R7.1
unnamed: D5.A, R8.1
unnamed: D6.A, R9.1
unnamed: D7.A, R10.1
unnamed: D8.A, R11.1
unnamed: R2.1, TS1.P$2
unnamed: R3.1, TS1.P$1
PWM_OUT: JP3.1, TP8.P$1, U1.7 (AN7/RC3)
RX: JP4.1, TP9.P$1, U1.5 (RX*/RC5)
SCL: JP2.1, TP7.P$1, U1.10 (RB7/SCK2/TX)
SCLK: U1.11 (RB6/SCK1), U2.7 (CLK)
SDA: JP1.1, TP6.P$1, U1.12 (RB5/AN11/SDI2/RX)
SDO: U1.9 (SDO1/AN9/RC7), U2.8 (SDI)
TX: JP5.1, TP10.P$1, U1.6 (TX*/RC4)
V+: C5.A (+), C6.1, J1.2, JP15.1, TP20.P$1, U2.5 (VDD)
V-: C7.C (-), C8.2, J2.2, JP8.1, TP13.P$1, U2.12 (VSS)
VIN: C1.A (+), JP6.1, TP11.P$1, U3.1 (IN), U3.3 (EN)
VPP: R1.1, TP1.P$1, U1.4 (RA3/VPP/!MCLR)
W1: JP13.1, TP18.P$1, U2.3 (W1)
W2: JP10.1, TP15.P$1, U2.15 (W2)

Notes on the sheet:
danjuliodesigns, LLC
V13
3 presses - Set I2C Address 4 presses - Start Cal procedure
IO Connections
ICSP
Analog Power
Default: Jumpers soldered.
PGD
PGC
Unsolder to connect V+
and V- to another supply.
Through Hole
SMD Pads
Joel Bartlett
Analog IC
Vin = 5-12V
DEFAULT I2C ADDRESS: 0x08
Digital Potentiometer Supply Single-ended (V- connected to GND): Min = 4.5V, Max = 16.5V Dual-ended: Min = +/-4.5V, Max = +/-5.5V For more info, see the Electrical Specifications section of the User Guide The maximum voltage potential between V- and V+ is 15 volts. V- maximum is -5V. V+ maximum is 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
Capacative Sense Pad
There are 64 available I2C addresses. See the Changing I2C Address section of the User Guide, for more info.

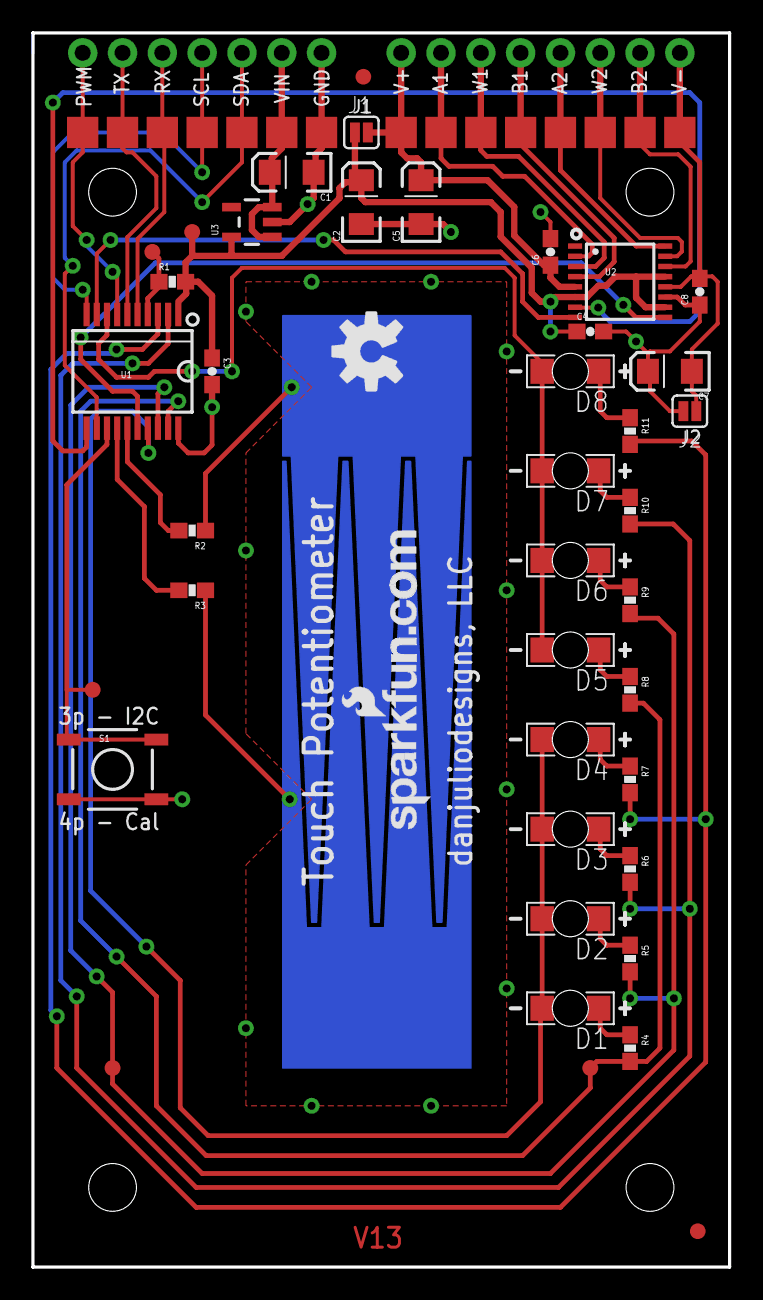
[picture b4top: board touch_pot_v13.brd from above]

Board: 2 copper layers, 44.5 x 78.7 mm, 78 parts (1 on the bottom side), 39 nets.

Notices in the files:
parts and their libraries:
SparkFun-Retired: Licensing:Creative Commons ShareAlike 4.0 International - https://creativecommons.org/licenses/by-sa/4.0
microbuilder: This work is placed in the public domain, and may be freely used for commercial and non-commercial work with the following conditions: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
